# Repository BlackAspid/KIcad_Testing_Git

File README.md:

# Kicad Testing Git
It's a test for work kicad with github. In this project the pcb is a module with the C.I. **X60008B**.

For this project the software used is **Kicad** an open source programm for electronic design.

## Component List
| Name | Package | Quantity |
| ------ | -------- | --------- |
| X60008B | SOIC-8 | 1 |
| Strip of pins X2 Male | Pin Header P2.54mm | 2 |
| 10uF Ceramic Capacitor | 0805 (2012 Metric) | 1 |
| 0.1uF Ceramic Capacitor | 0603 (1608 Metric) | 1 |
| 0.001uF Ceramic Capacitor | 0603 (1608 Metric) | 1 |

## Esquematic  Circuit

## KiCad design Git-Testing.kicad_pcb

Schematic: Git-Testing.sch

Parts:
C1: 10uF; C_0805_2012Metric
C2: 0.1uF; C_0603_1608Metric
C3: 0.001uF; C_0603_1608Metric
J1, J2: Conn_01x02_Male; PinHeader_1x02_P2.54mm_Vertical
PMIC1: X60008BIS8; SOIC-8_3.9x4.9mm_P1.27mm

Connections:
GND: C1.2, C2.2, C3.2, J1.2, J2.2, PMIC1.1, PMIC1.4
unnamed: C3.1, J2.1, PMIC1.6
VCC: C1.1, C2.1, J1.1, PMIC1.2

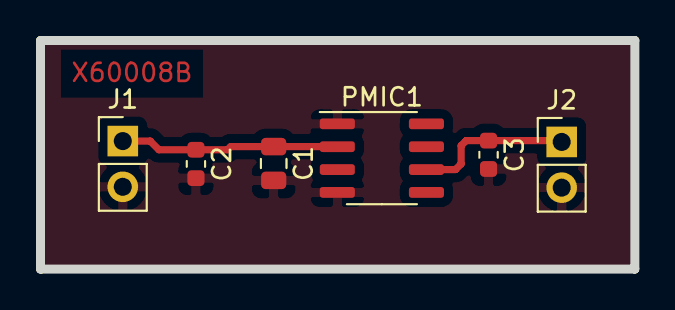
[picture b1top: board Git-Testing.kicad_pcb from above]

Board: 2 copper layers, 33.0 x 12.7 mm, 6 parts (0 on the bottom side), 3 nets.

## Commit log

2020-10-07 Added Kicad files with one resistor
2020-10-07 Added second resistor
2020-10-07 Erase all components
2020-10-11 Se agregaron dos archivos no modificados
2020-10-20 Se agregan nuevos archivos y se modifican los anteriores
2020-10-20 Se agrego la libreria del comparador de voltaje
2020-10-29 Se termino de conectar el esquematico
2020-10-29 Se agregaron los footprints a cada componente
2020-10-29 Se inicio con el diseño del pcb agregando las nets
2020-11-07 Se termino la pcb
2020-11-11 Se termino la placa de circuito electrico
2020-11-13 Modify Readme.md
